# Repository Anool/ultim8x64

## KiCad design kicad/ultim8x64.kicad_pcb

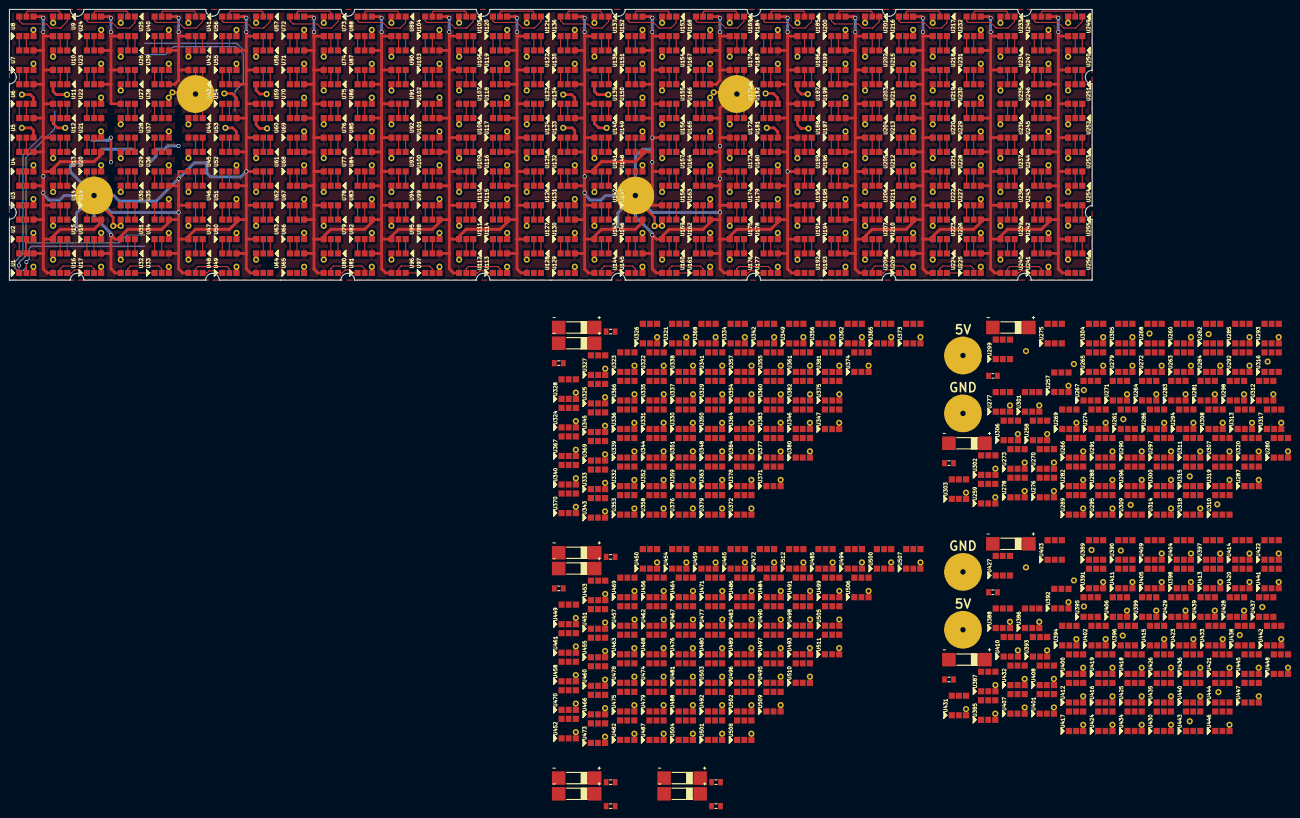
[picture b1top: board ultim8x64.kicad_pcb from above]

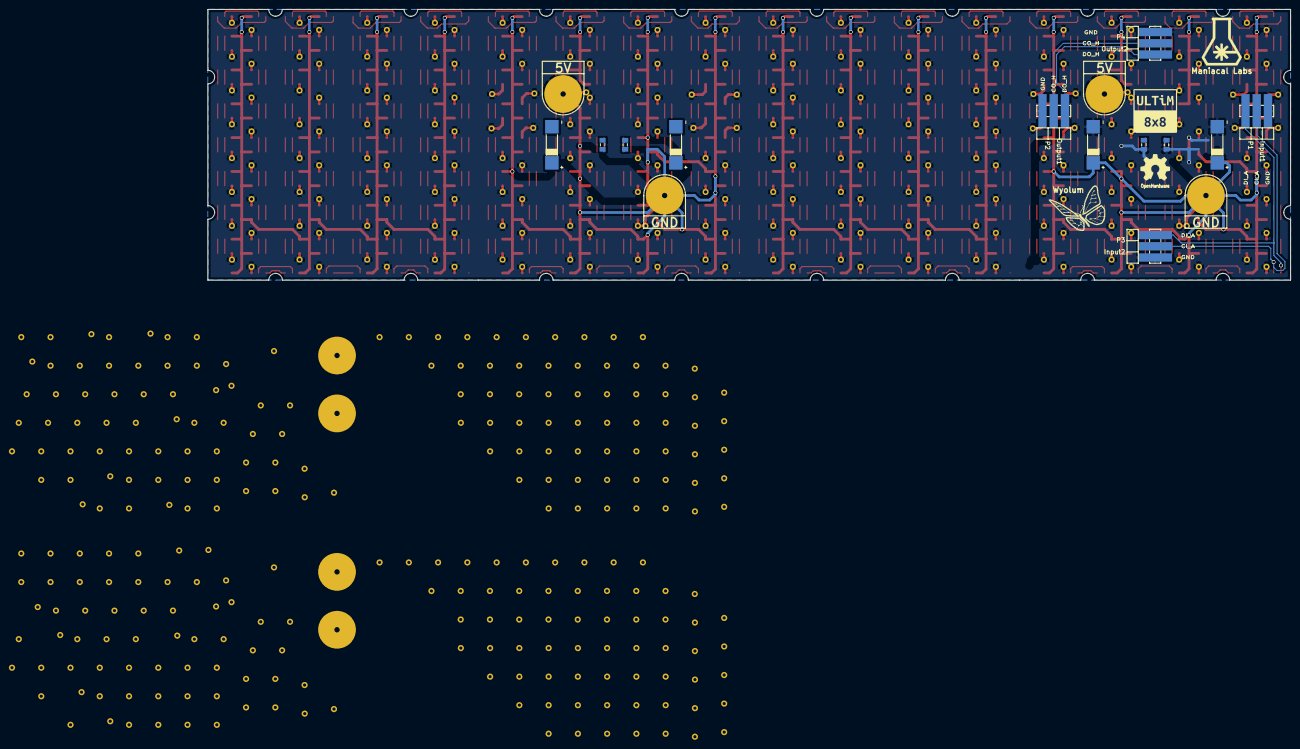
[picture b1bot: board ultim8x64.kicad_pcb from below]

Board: 2 copper layers, 243.8 x 61.0 mm, 560 parts (20 on the bottom side), 1036 nets.

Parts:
C1, C2, C5, C6, C9, C10, C13, C14, C17, C18, C21, C22, C25, C26, C29, C30: 47uF 20V; c_2917
C3, C4, C7, C8, C11, C12, C15, C16, C19, C20, C23, C24, C27, C28, C31, C32: 100nF; c_0805
L1: ULTiM8x8; logo_ultim8x8
L2: OSHW; OSHW_6mm
L3: Wyolum; logo_wyo_butterfly
L4: Maniacal Labs; logo_MLlabs
P1: Input1; header_3pos_smd_male
P2: Output1; header_3pos_smd_male
P3: Input2; header_3pos_smd_male
P4: Output2; header_3pos_smd_male
P5, P7, P9, P11: GND; PowerIn_stud
P6, P8, P10, P12: 5V; PowerIn_stud
U1, U2, U3, U4, U7, U8, U9, U10, U13, U14, U15, U16, U17, U18, U20, U21, U22, U23, U24, U25, U26, U27, U28, U29, U30, U31, U32, U33, U34, U35, U36, U37, U39, U40, U41, U42, U44, U45, U46, U47, U48, U49, U50, U51, U52, U55, U56, U57, U58, U61, U62, U63, U64, U65, U66, U67, U68, U69, U70, U71, U72, U73, U74, U75, U76, U77, U78, U79, U80, U81, U82, U83, U84, U85, U86, U87, U88, U89, U90, U91, U92, U93, U94, U95, U96, U97, U98, U99, U100, U101, U102, U103, U104, U105, U106, U107, U108, U109, U110, U111, U112, U113, U114, U115, U116, U117, U118, U119, U120, U121, U122, U123, U124, U125, U126, U127, U128, U129, U130, U131, U132, U135, U136, U137, U138, U141, U142, U143, U144, U145, U146, U148, U149, U150, U151, U152, U153, U154, U155, U156, U157, U158, U159, U160, U161, U162, U163, U164, U165, U167, U168, U169, U170, U172, U173, U174, U175, U176, U177, U178, U179, U180, U183, U184, U185, U186, U189, U190, U191, U192, U193, U194, U195, U196, U197, U198, U199, U200, U201, U202, U203, U204, U205, U206, U207, U208, U209, U210, U211, U212, U213, U214, U215, U216, U217, U218, U219, U220, U221, U222, U223, U224, U225, U226, U227, U228, U229, U230, U231, U232, U233, U234, U235, U236, U237, U238, U239, U240, U241, U242, U243, U244, U245, U246, U247, U248, U249, U250, U251, U252, U253, U254, U255, U256, U257, U258, U259, U260, U263, U264, U265, U266, U269, U270, U271, U272, U273, U274, U276, U277, U278, U279, U280, U281, U282, U283, U284, U285, U286, U287, U288, U289, U290, U291, U292, U293, U295, U296, U297, U298, U300, U301, U302, U303, U304, U305, U306, U307, U308, U311, U312, U313, U314, U317, U318, U319, U320, U321, U322, U323, U324, U325, U326, U327, U328, U329, U330, U331, U332, U333, U334, U335, U336, U337, U338, U339, U340, U341, U342, U343, U344, U345, U346, U347, U348, U349, U350, U351, U352, U353, U354, U355, U356, U357, U358, U359, U360, U361, U362, U363, U364, U365, U366, U367, U368, U369, U370, U371, U372, U373, U374, U375, U376, U377, U378, U379, U380, U381, U382, U383, U384, U385, U386, U387, U388, U391, U392, U393, U394, U397, U398, U399, U400, U401, U402, U404, U405, U406, U407, U408, U409, U410, U411, U412, U413, U414, U415, U416, U417, U418, U419, U420, U421, U423, U424, U425, U426, U428, U429, U430, U431, U432, U433, U434, U435, U436, U439, U440, U441, U442, U445, U446, U447, U448, U449, U450, U451, U452, U453, U454, U455, U456, U457, U458, U459, U460, U461, U462, U463, U464, U465, U466, U467, U468, U469, U470, U471, U472, U473, U474, U475, U476, U477, U478, U479, U480, U481, U482, U483, U484, U485, U486, U487, U488, U489, U490, U491, U492, U493, U494, U495, U496, U497, U498, U499, U500, U501, U502, U503, U504, U505, U506, U507, U508, U509, U510, U511, U512: APA102
U5, U133, U261, U389: APA102; APA102_U05
U6, U134, U262, U390: APA102; APA102_U06
U11, U139, U267, U395: APA102; APA102_U11
U12, U140, U268, U396: APA102; APA102_U12
U19, U147, U275, U403: APA102; APA102_U19
U38, U166, U294, U422: APA102; APA102_U38
U43, U171, U299, U427: APA102; APA102_U43
U53, U181, U309, U437: APA102; APA102_U53
U54, U182, U310, U438: APA102; APA102_U54
U59, U187, U315, U443: APA102; APA102_U59
U60, U188, U316, U444: APA102; APA102_U60

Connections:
/Row_A/5V: C1.1, C2.1, C3.1, C4.1, C9.1, C10.1, C11.1, C12.1, C17.1, C18.1, C19.1, C20.1, C25.1, C26.1, C27.1, C28.1, P5.1, P7.1, P9.1, P11.1, U1.4, U2.4, U3.4, U4.4, U5.4, U6.4, U7.4, U8.4, U9.4, U10.4, U11.4, U12.4, U13.4, U14.4, U15.4, U16.4, U17.4, U18.4, U19.4, U20.4, U21.4, U22.4, U23.4, U24.4, U25.4, U26.4, U27.4, U28.4, U29.4, U30.4, U31.4, U32.4, U33.4, U34.4, U35.4, U36.4, U37.4, U38.4, U39.4, U40.4, U41.4, U42.4, U43.4, U44.4, U45.4, U46.4, U47.4, U48.4, U49.4, U50.4, U51.4, U52.4, U53.4, U54.4, U55.4, U56.4, U57.4, U58.4, U59.4, U60.4, U61.4, U62.4, U63.4, U64.4, U65.4, U66.4, U67.4, U68.4, U69.4, U70.4, U71.4, U72.4, U73.4, U74.4, U75.4, U76.4, U77.4, U78.4, U79.4, U80.4, U81.4, U82.4, U83.4, U84.4, U85.4, U86.4, U87.4, U88.4, U89.4, U90.4, U91.4, U92.4, U93.4, U94.4, U95.4, U96.4, U97.4, U98.4, U99.4, U100.4, U101.4, U102.4, U103.4, U104.4, U105.4, U106.4, U107.4, U108.4, U109.4, U110.4, U111.4, U112.4, U113.4, U114.4, U115.4, U116.4, U117.4, U118.4, U119.4, U120.4, U121.4, U122.4, U123.4, U124.4, U125.4, U126.4, U127.4, U128.4, U129.4, U130.4, U131.4, U132.4, U133.4, U134.4, U135.4, U136.4, U137.4, U138.4, U139.4, U140.4, U141.4, U142.4, U143.4, U144.4, U145.4, U146.4, U147.4, U148.4, U149.4, U150.4, U151.4, U152.4, U153.4, U154.4, U155.4, U156.4, U157.4, U158.4, U159.4, U160.4, U161.4, U162.4, U163.4, U164.4, U165.4, U166.4, U167.4, U168.4, U169.4, U170.4, U171.4, U172.4, U173.4, U174.4, U175.4, U176.4, U177.4, U178.4, U179.4, U180.4, U181.4, U182.4, U183.4, U184.4, U185.4, U186.4, U187.4, U188.4, U189.4, U190.4, U191.4, U192.4, U193.4, U194.4, U195.4, U196.4, U197.4, U198.4, U199.4, U200.4, U201.4, U202.4, U203.4, U204.4, U205.4, U206.4, U207.4, U208.4, U209.4, U210.4, U211.4, U212.4, U213.4, U214.4, U215.4, U216.4, U217.4, U218.4, U219.4, U220.4, U221.4, U222.4, U223.4, U224.4, U225.4, U226.4, U227.4, U228.4, U229.4, U230.4, U231.4, U232.4, U233.4, U234.4, U235.4, U236.4, U237.4, U238.4, U239.4, U240.4, U241.4, U242.4, U243.4, U244.4, U245.4, U246.4, U247.4, U248.4, U249.4, U250.4, U251.4, U252.4, U253.4, U254.4, U255.4, U256.4, U257.4, U258.4, U259.4, U260.4, U261.4, U262.4, U263.4, U264.4, U265.4, U266.4, U267.4, U268.4, U269.4, U270.4, U271.4, U272.4, U273.4, U274.4, U275.4, U276.4, U277.4, U278.4, U279.4, U280.4, U281.4, U282.4, U283.4, U284.4, U285.4, U286.4, U287.4, U288.4, U289.4, U290.4, U291.4, U292.4, U293.4, U294.4, U295.4, U296.4, U297.4, U298.4, U299.4, U300.4, U301.4, U302.4, U303.4, U304.4, U305.4, U306.4, U307.4, U308.4, U309.4, U310.4, U311.4, U312.4, U313.4, U314.4, U315.4, U316.4, U317.4, U318.4, U319.4, U320.4, U321.4, U322.4, U323.4, U324.4, U325.4, U326.4, U327.4, U328.4, U329.4, U330.4, U331.4, U332.4, U333.4, U334.4, U335.4, U336.4, U337.4, U338.4, U339.4, U340.4, U341.4, U342.4, U343.4, U344.4, U345.4, U346.4, U347.4, U348.4, U349.4, U350.4, U351.4, U352.4, U353.4, U354.4, U355.4, U356.4, U357.4, U358.4, U359.4, U360.4, U361.4, U362.4, U363.4, U364.4, U365.4, U366.4, U367.4, U368.4, U369.4, U370.4, U371.4, U372.4, U373.4, U374.4, U375.4, U376.4, U377.4, U378.4, U379.4, U380.4, U381.4, U382.4, U383.4, U384.4, U385.4, U386.4, U387.4, U388.4, U389.4, U390.4, U391.4, U392.4, U393.4, U394.4, U395.4, U396.4, U397.4, U398.4, U399.4, U400.4, U401.4, U402.4, U403.4, U404.4, U405.4, U406.4, U407.4, U408.4, U409.4, U410.4, U411.4, U412.4, U413.4, U414.4, U415.4, U416.4, U417.4, U418.4, U419.4, U420.4, U421.4, U422.4, U423.4, U424.4, U425.4, U426.4, U427.4, U428.4, U429.4, U430.4, U431.4, U432.4, U433.4, U434.4, U435.4, U436.4, U437.4, U438.4, U439.4, U440.4, U441.4, U442.4, U443.4, U444.4, U445.4, U446.4, U447.4, U448.4, U449.4, U450.4, U451.4, U452.4, U453.4, U454.4, U455.4, U456.4, U457.4, U458.4, U459.4, U460.4, U461.4, U462.4, U463.4, U464.4, U465.4, U466.4, U467.4, U468.4, U469.4, U470.4, U471.4, U472.4, U473.4, U474.4, U475.4, U476.4, U477.4, U478.4, U479.4, U480.4, U481.4, U482.4, U483.4, U484.4, U485.4, U486.4, U487.4, U488.4, U489.4, U490.4, U491.4, U492.4, U493.4, U494.4, U495.4, U496.4, U497.4, U498.4, U499.4, U500.4, U501.4, U502.4, U503.4, U504.4, U505.4, U506.4, U507.4, U508.4, U509.4, U510.4, U511.4, U512.4
/Row_A/CI_A: P1.2, P3.2, U1.2
/Row_A/CI_B: U64.5, U65.2
/Row_A/DI_A: P1.1, P3.1, U1.1
/Row_A/DI_B: U64.6, U65.1
/Row_B/CI_C: U128.5, U129.2
/Row_B/DI_C: U128.6, U129.1
/Row_C/CI_D: U192.5, U193.2
/Row_C/DI_D: U192.6, U193.1
/Row_D/CI_E: U256.5, U257.2
/Row_D/DI_E: U256.6, U257.1
/Row_E/CI_F: U320.5, U321.2
/Row_E/DI_F: U320.6, U321.1
/Row_F/CI_G: U384.5, U385.2
/Row_F/DI_G: U384.6, U385.1
/Row_G/CI_H: U448.5, U449.2
/Row_G/DI_H: U448.6, U449.1
/Row_H/CO_H: P2.2, P4.2, U512.5
/Row_H/DO_H: P2.3, P4.3, U512.6
GND: C1.2, C2.2, C3.2, C4.2, C9.2, C10.2, C11.2, C12.2, C17.2, C18.2, C19.2, C20.2, C25.2, C26.2, C27.2, C28.2, P1.3, P2.1, P3.3, P4.1, P6.1, P8.1, P10.1, P12.1, U1.3, U2.3, U3.3, U4.3, U5.3, U6.3, U7.3, U8.3, U9.3, U10.3, U11.3, U12.3, U13.3, U14.3, U15.3, U16.3, U17.3, U18.3, U19.3, U20.3, U21.3, U22.3, U23.3, U24.3, U25.3, U26.3, U27.3, U28.3, U29.3, U30.3, U31.3, U32.3, U33.3, U34.3, U35.3, U36.3, U37.3, U38.3, U39.3, U40.3, U41.3, U42.3, U43.3, U44.3, U45.3, U46.3, U47.3, U48.3, U49.3, U50.3, U51.3, U52.3, U53.3, U54.3, U55.3, U56.3, U57.3, U58.3, U59.3, U60.3, U61.3, U62.3, U63.3, U64.3, U65.3, U66.3, U67.3, U68.3, U69.3, U70.3, U71.3, U72.3, U73.3, U74.3, U75.3, U76.3, U77.3, U78.3, U79.3, U80.3, U81.3, U82.3, U83.3, U84.3, U85.3, U86.3, U87.3, U88.3, U89.3, U90.3, U91.3, U92.3, U93.3, U94.3, U95.3, U96.3, U97.3, U98.3, U99.3, U100.3, U101.3, U102.3, U103.3, U104.3, U105.3, U106.3, U107.3, U108.3, U109.3, U110.3, U111.3, U112.3, U113.3, U114.3, U115.3, U116.3, U117.3, U118.3, U119.3, U120.3, U121.3, U122.3, U123.3, U124.3, U125.3, U126.3, U127.3, U128.3, U129.3, U130.3, U131.3, U132.3, U133.3, U134.3, U135.3, U136.3, U137.3, U138.3, U139.3, U140.3, U141.3, U142.3, U143.3, U144.3, U145.3, U146.3, U147.3, U148.3, U149.3, U150.3, U151.3, U152.3, U153.3, U154.3, U155.3, U156.3, U157.3, U158.3, U159.3, U160.3, U161.3, U162.3, U163.3, U164.3, U165.3, U166.3, U167.3, U168.3, U169.3, U170.3, U171.3, U172.3, U173.3, U174.3, U175.3, U176.3, U177.3, U178.3, U179.3, U180.3, U181.3, U182.3, U183.3, U184.3, U185.3, U186.3, U187.3, U188.3, U189.3, U190.3, U191.3, U192.3, U193.3, U194.3, U195.3, U196.3, U197.3, U198.3, U199.3, U200.3, U201.3, U202.3, U203.3, U204.3, U205.3, U206.3, U207.3, U208.3, U209.3, U210.3, U211.3, U212.3, U213.3, U214.3, U215.3, U216.3, U217.3, U218.3, U219.3, U220.3, U221.3, U222.3, U223.3, U224.3, U225.3, U226.3, U227.3, U228.3, U229.3, U230.3, U231.3, U232.3, U233.3, U234.3, U235.3, U236.3, U237.3, U238.3, U239.3, U240.3, U241.3, U242.3, U243.3, U244.3, U245.3, U246.3, U247.3, U248.3, U249.3, U250.3, U251.3, U252.3, U253.3, U254.3, U255.3, U256.3, U257.3, U258.3, U259.3, U260.3, U261.3, U262.3, U263.3, U264.3, U265.3, U266.3, U267.3, U268.3, U269.3, U270.3, U271.3, U272.3, U273.3, U274.3, U275.3, U276.3, U277.3, U278.3, U279.3, U280.3, U281.3, U282.3, U283.3, U284.3, U285.3, U286.3, U287.3, U288.3, U289.3, U290.3, U291.3, U292.3, U293.3, U294.3, U295.3, U296.3, U297.3, U298.3, U299.3, U300.3, U301.3, U302.3, U303.3, U304.3, U305.3, U306.3, U307.3, U308.3, U309.3, U310.3, U311.3, U312.3, U313.3, U314.3, U315.3, U316.3, U317.3, U318.3, U319.3, U320.3, U321.3, U322.3, U323.3, U324.3, U325.3, U326.3, U327.3, U328.3, U329.3, U330.3, U331.3, U332.3, U333.3, U334.3, U335.3, U336.3, U337.3, U338.3, U339.3, U340.3, U341.3, U342.3, U343.3, U344.3, U345.3, U346.3, U347.3, U348.3, U349.3, U350.3, U351.3, U352.3, U353.3, U354.3, U355.3, U356.3, U357.3, U358.3, U359.3, U360.3, U361.3, U362.3, U363.3, U364.3, U365.3, U366.3, U367.3, U368.3, U369.3, U370.3, U371.3, U372.3, U373.3, U374.3, U375.3, U376.3, U377.3, U378.3, U379.3, U380.3, U381.3, U382.3, U383.3, U384.3, U385.3, U386.3, U387.3, U388.3, U389.3, U390.3, U391.3, U392.3, U393.3, U394.3, U395.3, U396.3, U397.3, U398.3, U399.3, U400.3, U401.3, U402.3, U403.3, U404.3, U405.3, U406.3, U407.3, U408.3, U409.3, U410.3, U411.3, U412.3, U413.3, U414.3, U415.3, U416.3, U417.3, U418.3, U419.3, U420.3, U421.3, U422.3, U423.3, U424.3, U425.3, U426.3, U427.3, U428.3, U429.3, U430.3, U431.3, U432.3, U433.3, U434.3, U435.3, U436.3, U437.3, U438.3, U439.3, U440.3, U441.3, U442.3, U443.3, U444.3, U445.3, U446.3, U447.3, U448.3, U449.3, U450.3, U451.3, U452.3, U453.3, U454.3, U455.3, U456.3, U457.3, U458.3, U459.3, U460.3, U461.3, U462.3, U463.3, U464.3, U465.3, U466.3, U467.3, U468.3, U469.3, U470.3, U471.3, U472.3, U473.3, U474.3, U475.3, U476.3, U477.3, U478.3, U479.3, U480.3, U481.3, U482.3, U483.3, U484.3, U485.3, U486.3, U487.3, U488.3, U489.3, U490.3, U491.3, U492.3, U493.3, U494.3, U495.3, U496.3, U497.3, U498.3, U499.3, U500.3, U501.3, U502.3, U503.3, U504.3, U505.3, U506.3, U507.3, U508.3, U509.3, U510.3, U511.3, U512.3
unnamed: C5.1, C6.1, C7.1, C8.1
unnamed: C5.2, C6.2, C7.2, C8.2
unnamed: C13.1, C14.1, C15.1, C16.1
unnamed: C13.2, C14.2, C15.2, C16.2
unnamed: C21.1, C22.1, C23.1, C24.1
unnamed: C21.2, C22.2, C23.2, C24.2
unnamed: C29.1, C30.1, C31.1, C32.1
unnamed: C29.2, C30.2, C31.2, C32.2
unnamed: U1.5, U2.2
unnamed: U1.6, U2.1
unnamed: U2.5, U3.2
unnamed: U2.6, U3.1
unnamed: U3.5, U4.2
unnamed: U3.6, U4.1
unnamed: U4.5, U5.2
unnamed: U4.6, U5.1
unnamed: U5.5, U6.2
unnamed: U5.6, U6.1
unnamed: U6.5, U7.2
unnamed: U6.6, U7.1
unnamed: U7.5, U8.2
unnamed: U7.6, U8.1
unnamed: U8.5, U9.2
unnamed: U8.6, U9.1
unnamed: U9.6, U10.1
unnamed: U9.5, U10.2
unnamed: U10.5, U11.2
unnamed: U10.6, U11.1
unnamed: U11.5, U12.2
unnamed: U11.6, U12.1
unnamed: U12.5, U13.2
unnamed: U12.6, U13.1
unnamed: U13.5, U14.2
unnamed: U13.6, U14.1
unnamed: U14.5, U15.2
unnamed: U14.6, U15.1
unnamed: U15.5, U16.2
unnamed: U15.6, U16.1
unnamed: U16.5, U17.2
unnamed: U16.6, U17.1
unnamed: U17.5, U18.2
unnamed: U17.6, U18.1
unnamed: U18.5, U19.2
unnamed: U18.6, U19.1
unnamed: U19.5, U20.2
unnamed: U19.6, U20.1
unnamed: U20.5, U21.2
unnamed: U20.6, U21.1
unnamed: U21.5, U22.2
unnamed: U21.6, U22.1
unnamed: U22.5, U23.2
unnamed: U22.6, U23.1
unnamed: U23.5, U24.2
unnamed: U23.6, U24.1
unnamed: U24.5, U25.2
unnamed: U24.6, U25.1
unnamed: U25.5, U26.2
unnamed: U25.6, U26.1
unnamed: U26.5, U27.2
unnamed: U26.6, U27.1
unnamed: U27.5, U28.2
unnamed: U27.6, U28.1
unnamed: U28.5, U29.2
unnamed: U28.6, U29.1
unnamed: U29.5, U30.2
unnamed: U29.6, U30.1
unnamed: U30.5, U31.2
unnamed: U30.6, U31.1
unnamed: U31.5, U32.2
unnamed: U31.6, U32.1
unnamed: U32.5, U33.2
unnamed: U32.6, U33.1
unnamed: U33.5, U34.2
unnamed: U33.6, U34.1
unnamed: U34.5, U35.2
unnamed: U34.6, U35.1
unnamed: U35.5, U36.2
unnamed: U35.6, U36.1
unnamed: U36.5, U37.2
unnamed: U36.6, U37.1
unnamed: U37.5, U38.2
unnamed: U37.6, U38.1
unnamed: U38.5, U39.2
unnamed: U38.6, U39.1
unnamed: U39.5, U40.2
unnamed: U39.6, U40.1
unnamed: U40.5, U41.2
unnamed: U40.6, U41.1
unnamed: U41.5, U42.2
unnamed: U41.6, U42.1
unnamed: U42.5, U43.2
unnamed: U42.6, U43.1
unnamed: U43.5, U44.2
unnamed: U43.6, U44.1
unnamed: U44.5, U45.2
unnamed: U44.6, U45.1
unnamed: U45.5, U46.2
unnamed: U45.6, U46.1
unnamed: U46.5, U47.2
unnamed: U46.6, U47.1
unnamed: U47.5, U48.2
unnamed: U47.6, U48.1
unnamed: U48.5, U49.2
unnamed: U48.6, U49.1
unnamed: U49.5, U50.2
unnamed: U49.6, U50.1
unnamed: U50.5, U51.2
unnamed: U50.6, U51.1
unnamed: U51.5, U52.2
unnamed: U51.6, U52.1
unnamed: U52.5, U53.2
unnamed: U52.6, U53.1
unnamed: U53.5, U54.2
unnamed: U53.6, U54.1
unnamed: U54.5, U55.2
unnamed: U54.6, U55.1
unnamed: U55.5, U56.2
unnamed: U55.6, U56.1
unnamed: U56.5, U57.2
unnamed: U56.6, U57.1
unnamed: U57.5, U58.2
unnamed: U57.6, U58.1
unnamed: U58.5, U59.2
unnamed: U58.6, U59.1
unnamed: U59.5, U60.2
unnamed: U59.6, U60.1
unnamed: U60.5, U61.2
unnamed: U60.6, U61.1
unnamed: U61.5, U62.2
unnamed: U61.6, U62.1
unnamed: U62.5, U63.2
unnamed: U62.6, U63.1
unnamed: U63.5, U64.2
unnamed: U63.6, U64.1
unnamed: U65.5, U66.2
unnamed: U65.6, U66.1
unnamed: U66.5, U67.2
unnamed: U66.6, U67.1
unnamed: U67.5, U68.2
unnamed: U67.6, U68.1
unnamed: U68.5, U69.2
unnamed: U68.6, U69.1
unnamed: U69.5, U70.2
unnamed: U69.6, U70.1
unnamed: U70.5, U71.2
unnamed: U70.6, U71.1
unnamed: U71.5, U72.2
unnamed: U71.6, U72.1
unnamed: U72.5, U73.2
unnamed: U72.6, U73.1
unnamed: U73.5, U74.2
unnamed: U73.6, U74.1
unnamed: U74.5, U75.2
unnamed: U74.6, U75.1
unnamed: U75.5, U76.2
unnamed: U75.6, U76.1
unnamed: U76.5, U77.2
unnamed: U76.6, U77.1
unnamed: U77.5, U78.2
unnamed: U77.6, U78.1
unnamed: U78.5, U79.2
unnamed: U78.6, U79.1
unnamed: U79.5, U80.2
unnamed: U79.6, U80.1
unnamed: U80.5, U81.2
unnamed: U80.6, U81.1
unnamed: U81.5, U82.2
unnamed: U81.6, U82.1
unnamed: U82.5, U83.2
unnamed: U82.6, U83.1
unnamed: U83.5, U84.2
unnamed: U83.6, U84.1
unnamed: U84.5, U85.2
unnamed: U84.6, U85.1
unnamed: U85.5, U86.2
unnamed: U85.6, U86.1
unnamed: U86.5, U87.2
unnamed: U86.6, U87.1
unnamed: U87.5, U88.2
unnamed: U87.6, U88.1
unnamed: U88.5, U89.2
unnamed: U88.6, U89.1
unnamed: U89.5, U90.2
unnamed: U89.6, U90.1
unnamed: U90.5, U91.2
unnamed: U90.6, U91.1
unnamed: U91.5, U92.2
unnamed: U91.6, U92.1
unnamed: U92.5, U93.2
unnamed: U92.6, U93.1
unnamed: U93.5, U94.2
unnamed: U93.6, U94.1
unnamed: U94.5, U95.2
unnamed: U94.6, U95.1
unnamed: U95.5, U96.2
unnamed: U95.6, U96.1
unnamed: U96.5, U97.2
unnamed: U96.6, U97.1
unnamed: U97.5, U98.2
unnamed: U97.6, U98.1
unnamed: U98.5, U99.2
unnamed: U98.6, U99.1
unnamed: U99.6, U100.1
unnamed: U99.5, U100.2
unnamed: U100.5, U101.2
unnamed: U100.6, U101.1
unnamed: U101.5, U102.2
unnamed: U101.6, U102.1
unnamed: U102.5, U103.2
unnamed: U102.6, U103.1
unnamed: U103.5, U104.2
unnamed: U103.6, U104.1
unnamed: U104.5, U105.2
unnamed: U104.6, U105.1
unnamed: U105.5, U106.2
unnamed: U105.6, U106.1
unnamed: U106.5, U107.2
unnamed: U106.6, U107.1
unnamed: U107.5, U108.2
unnamed: U107.6, U108.1
unnamed: U108.5, U109.2
unnamed: U108.6, U109.1
unnamed: U109.5, U110.2
unnamed: U109.6, U110.1
unnamed: U110.5, U111.2
unnamed: U110.6, U111.1
unnamed: U111.5, U112.2
unnamed: U111.6, U112.1
unnamed: U112.5, U113.2
unnamed: U112.6, U113.1
unnamed: U113.5, U114.2
unnamed: U113.6, U114.1
unnamed: U114.5, U115.2
unnamed: U114.6, U115.1
unnamed: U115.5, U116.2
unnamed: U115.6, U116.1
unnamed: U116.5, U117.2
unnamed: U116.6, U117.1
unnamed: U117.5, U118.2
unnamed: U117.6, U118.1
unnamed: U118.5, U119.2
unnamed: U118.6, U119.1
unnamed: U119.5, U120.2
unnamed: U119.6, U120.1
unnamed: U120.5, U121.2
unnamed: U120.6, U121.1
unnamed: U121.5, U122.2
unnamed: U121.6, U122.1
unnamed: U122.5, U123.2
unnamed: U122.6, U123.1
unnamed: U123.5, U124.2
unnamed: U123.6, U124.1
unnamed: U124.5, U125.2
unnamed: U124.6, U125.1
unnamed: U125.5, U126.2
unnamed: U125.6, U126.1
unnamed: U126.5, U127.2
unnamed: U126.6, U127.1
unnamed: U127.5, U128.2
unnamed: U127.6, U128.1
unnamed: U129.5, U130.2
unnamed: U129.6, U130.1
unnamed: U130.5, U131.2
unnamed: U130.6, U131.1
unnamed: U131.5, U132.2
unnamed: U131.6, U132.1
unnamed: U132.5, U133.2
unnamed: U132.6, U133.1
unnamed: U133.5, U134.2
unnamed: U133.6, U134.1
unnamed: U134.5, U135.2
unnamed: U134.6, U135.1
unnamed: U135.5, U136.2
unnamed: U135.6, U136.1
unnamed: U136.5, U137.2
unnamed: U136.6, U137.1
unnamed: U137.5, U138.2
unnamed: U137.6, U138.1
unnamed: U138.5, U139.2
unnamed: U138.6, U139.1
unnamed: U139.5, U140.2
unnamed: U139.6, U140.1
unnamed: U140.5, U141.2
unnamed: U140.6, U141.1
unnamed: U141.5, U142.2
unnamed: U141.6, U142.1
unnamed: U142.5, U143.2
unnamed: U142.6, U143.1
unnamed: U143.5, U144.2
unnamed: U143.6, U144.1
unnamed: U144.5, U145.2
unnamed: U144.6, U145.1
unnamed: U145.5, U146.2
unnamed: U145.6, U146.1
unnamed: U146.5, U147.2
unnamed: U146.6, U147.1
unnamed: U147.5, U148.2
unnamed: U147.6, U148.1
unnamed: U148.5, U149.2
unnamed: U148.6, U149.1
unnamed: U149.5, U150.2
unnamed: U149.6, U150.1
unnamed: U150.5, U151.2
unnamed: U150.6, U151.1
unnamed: U151.5, U152.2
unnamed: U151.6, U152.1
unnamed: U152.5, U153.2
unnamed: U152.6, U153.1
unnamed: U153.5, U154.2
unnamed: U153.6, U154.1
unnamed: U154.5, U155.2
unnamed: U154.6, U155.1
unnamed: U155.5, U156.2
unnamed: U155.6, U156.1
unnamed: U156.5, U157.2
unnamed: U156.6, U157.1
unnamed: U157.5, U158.2
unnamed: U157.6, U158.1
unnamed: U158.5, U159.2
unnamed: U158.6, U159.1
unnamed: U159.5, U160.2
unnamed: U159.6, U160.1
unnamed: U160.5, U161.2
unnamed: U160.6, U161.1
unnamed: U161.5, U162.2
unnamed: U161.6, U162.1
unnamed: U162.5, U163.2
unnamed: U162.6, U163.1
unnamed: U163.5, U164.2
unnamed: U163.6, U164.1
unnamed: U164.5, U165.2
unnamed: U164.6, U165.1
unnamed: U165.5, U166.2
unnamed: U165.6, U166.1
unnamed: U166.5, U167.2
unnamed: U166.6, U167.1
unnamed: U167.5, U168.2
unnamed: U167.6, U168.1
unnamed: U168.5, U169.2
unnamed: U168.6, U169.1
unnamed: U169.5, U170.2
unnamed: U169.6, U170.1
unnamed: U170.5, U171.2
unnamed: U170.6, U171.1
unnamed: U171.5, U172.2
unnamed: U171.6, U172.1
unnamed: U172.5, U173.2
unnamed: U172.6, U173.1
unnamed: U173.5, U174.2
unnamed: U173.6, U174.1
unnamed: U174.5, U175.2
unnamed: U174.6, U175.1
unnamed: U175.5, U176.2
unnamed: U175.6, U176.1
unnamed: U176.5, U177.2
unnamed: U176.6, U177.1
unnamed: U177.5, U178.2
unnamed: U177.6, U178.1
unnamed: U178.5, U179.2
unnamed: U178.6, U179.1
unnamed: U179.5, U180.2
unnamed: U179.6, U180.1
unnamed: U180.5, U181.2
unnamed: U180.6, U181.1
unnamed: U181.5, U182.2
unnamed: U181.6, U182.1
unnamed: U182.5, U183.2
unnamed: U182.6, U183.1
unnamed: U183.5, U184.2
unnamed: U183.6, U184.1
unnamed: U184.5, U185.2
unnamed: U184.6, U185.1
unnamed: U185.5, U186.2
unnamed: U185.6, U186.1
unnamed: U186.5, U187.2
unnamed: U186.6, U187.1
unnamed: U187.5, U188.2
unnamed: U187.6, U188.1
unnamed: U188.5, U189.2
unnamed: U188.6, U189.1
unnamed: U189.5, U190.2
unnamed: U189.6, U190.1
unnamed: U190.5, U191.2
unnamed: U190.6, U191.1
unnamed: U191.5, U192.2
unnamed: U191.6, U192.1
unnamed: U193.5, U194.2
unnamed: U193.6, U194.1
unnamed: U194.5, U195.2
unnamed: U194.6, U195.1
unnamed: U195.5, U196.2
unnamed: U195.6, U196.1
unnamed: U196.5, U197.2
unnamed: U196.6, U197.1
unnamed: U197.5, U198.2
unnamed: U197.6, U198.1
unnamed: U198.5, U199.2
unnamed: U198.6, U199.1
unnamed: U199.5, U200.2
unnamed: U199.6, U200.1
unnamed: U200.5, U201.2
unnamed: U200.6, U201.1
unnamed: U201.5, U202.2
unnamed: U201.6, U202.1
unnamed: U202.5, U203.2
unnamed: U202.6, U203.1
unnamed: U203.5, U204.2
unnamed: U203.6, U204.1
unnamed: U204.5, U205.2
unnamed: U204.6, U205.1
unnamed: U205.5, U206.2
unnamed: U205.6, U206.1
unnamed: U206.5, U207.2
unnamed: U206.6, U207.1
unnamed: U207.5, U208.2
unnamed: U207.6, U208.1
unnamed: U208.5, U209.2
unnamed: U208.6, U209.1
unnamed: U209.5, U210.2
unnamed: U209.6, U210.1
unnamed: U210.5, U211.2
unnamed: U210.6, U211.1
unnamed: U211.5, U212.2
unnamed: U211.6, U212.1
unnamed: U212.5, U213.2
unnamed: U212.6, U213.1
unnamed: U213.5, U214.2
unnamed: U213.6, U214.1
unnamed: U214.5, U215.2
unnamed: U214.6, U215.1
unnamed: U215.5, U216.2
unnamed: U215.6, U216.1
unnamed: U216.5, U217.2
unnamed: U216.6, U217.1
unnamed: U217.5, U218.2
unnamed: U217.6, U218.1
unnamed: U218.5, U219.2
unnamed: U218.6, U219.1
unnamed: U219.5, U220.2
unnamed: U219.6, U220.1
unnamed: U220.5, U221.2
unnamed: U220.6, U221.1
unnamed: U221.5, U222.2
unnamed: U221.6, U222.1
unnamed: U222.5, U223.2
unnamed: U222.6, U223.1
unnamed: U223.5, U224.2
unnamed: U223.6, U224.1
unnamed: U224.5, U225.2
unnamed: U224.6, U225.1
unnamed: U225.5, U226.2
unnamed: U225.6, U226.1
unnamed: U226.5, U227.2
unnamed: U226.6, U227.1
unnamed: U227.5, U228.2
unnamed: U227.6, U228.1
unnamed: U228.5, U229.2
unnamed: U228.6, U229.1
unnamed: U229.5, U230.2
unnamed: U229.6, U230.1
unnamed: U230.5, U231.2
unnamed: U230.6, U231.1
unnamed: U231.5, U232.2
unnamed: U231.6, U232.1
unnamed: U232.5, U233.2
unnamed: U232.6, U233.1
unnamed: U233.5, U234.2
unnamed: U233.6, U234.1
unnamed: U234.5, U235.2
unnamed: U234.6, U235.1
unnamed: U235.5, U236.2
unnamed: U235.6, U236.1
unnamed: U236.5, U237.2
unnamed: U236.6, U237.1
unnamed: U237.5, U238.2
unnamed: U237.6, U238.1
unnamed: U238.5, U239.2
unnamed: U238.6, U239.1
unnamed: U239.5, U240.2
unnamed: U239.6, U240.1
unnamed: U240.5, U241.2
unnamed: U240.6, U241.1
unnamed: U241.5, U242.2
unnamed: U241.6, U242.1
unnamed: U242.5, U243.2
unnamed: U242.6, U243.1
unnamed: U243.5, U244.2
unnamed: U243.6, U244.1
unnamed: U244.5, U245.2
unnamed: U244.6, U245.1
unnamed: U245.5, U246.2
unnamed: U245.6, U246.1
unnamed: U246.5, U247.2
unnamed: U246.6, U247.1
unnamed: U247.5, U248.2
unnamed: U247.6, U248.1
unnamed: U248.5, U249.2
unnamed: U248.6, U249.1
unnamed: U249.5, U250.2
unnamed: U249.6, U250.1
unnamed: U250.5, U251.2
unnamed: U250.6, U251.1
unnamed: U251.5, U252.2
unnamed: U251.6, U252.1
unnamed: U252.5, U253.2
unnamed: U252.6, U253.1
unnamed: U253.5, U254.2
unnamed: U253.6, U254.1
unnamed: U254.5, U255.2
unnamed: U254.6, U255.1
unnamed: U255.5, U256.2
unnamed: U255.6, U256.1
unnamed: U257.5, U258.2
unnamed: U257.6, U258.1
unnamed: U258.5, U259.2
unnamed: U258.6, U259.1
unnamed: U259.5, U260.2
unnamed: U259.6, U260.1
unnamed: U260.5, U261.2
unnamed: U260.6, U261.1
unnamed: U261.5, U262.2
unnamed: U261.6, U262.1
unnamed: U262.5, U263.2
unnamed: U262.6, U263.1
unnamed: U263.5, U264.2
unnamed: U263.6, U264.1
unnamed: U264.5, U265.2
unnamed: U264.6, U265.1
unnamed: U265.5, U266.2
unnamed: U265.6, U266.1
unnamed: U266.5, U267.2
unnamed: U266.6, U267.1
unnamed: U267.5, U268.2
unnamed: U267.6, U268.1
unnamed: U268.5, U269.2
unnamed: U268.6, U269.1
unnamed: U269.5, U270.2
unnamed: U269.6, U270.1
unnamed: U270.5, U271.2
unnamed: U270.6, U271.1
unnamed: U271.5, U272.2
unnamed: U271.6, U272.1
unnamed: U272.5, U273.2
unnamed: U272.6, U273.1
unnamed: U273.5, U274.2
unnamed: U273.6, U274.1
unnamed: U274.5, U275.2
unnamed: U274.6, U275.1
unnamed: U275.5, U276.2
unnamed: U275.6, U276.1
unnamed: U276.5, U277.2
unnamed: U276.6, U277.1
unnamed: U277.5, U278.2
unnamed: U277.6, U278.1
unnamed: U278.5, U279.2
unnamed: U278.6, U279.1
unnamed: U279.5, U280.2
unnamed: U279.6, U280.1
unnamed: U280.5, U281.2
unnamed: U280.6, U281.1
unnamed: U281.5, U282.2
unnamed: U281.6, U282.1
unnamed: U282.5, U283.2
unnamed: U282.6, U283.1
unnamed: U283.5, U284.2
unnamed: U283.6, U284.1
unnamed: U284.5, U285.2
unnamed: U284.6, U285.1
unnamed: U285.5, U286.2
unnamed: U285.6, U286.1
unnamed: U286.5, U287.2
unnamed: U286.6, U287.1
unnamed: U287.5, U288.2
unnamed: U287.6, U288.1
unnamed: U288.5, U289.2
unnamed: U288.6, U289.1
unnamed: U289.5, U290.2
unnamed: U289.6, U290.1
unnamed: U290.5, U291.2
unnamed: U290.6, U291.1
unnamed: U291.5, U292.2
unnamed: U291.6, U292.1
unnamed: U292.5, U293.2
unnamed: U292.6, U293.1
unnamed: U293.5, U294.2
unnamed: U293.6, U294.1
unnamed: U294.5, U295.2
unnamed: U294.6, U295.1
unnamed: U295.5, U296.2
unnamed: U295.6, U296.1
unnamed: U296.5, U297.2
unnamed: U296.6, U297.1
unnamed: U297.5, U298.2
unnamed: U297.6, U298.1
unnamed: U298.5, U299.2
unnamed: U298.6, U299.1
unnamed: U299.5, U300.2
unnamed: U299.6, U300.1
unnamed: U300.5, U301.2
unnamed: U300.6, U301.1
unnamed: U301.5, U302.2
unnamed: U301.6, U302.1
unnamed: U302.5, U303.2
unnamed: U302.6, U303.1
unnamed: U303.5, U304.2
unnamed: U303.6, U304.1
unnamed: U304.5, U305.2
unnamed: U304.6, U305.1
unnamed: U305.5, U306.2
unnamed: U305.6, U306.1
unnamed: U306.5, U307.2
unnamed: U306.6, U307.1
unnamed: U307.5, U308.2
unnamed: U307.6, U308.1
unnamed: U308.5, U309.2
unnamed: U308.6, U309.1
unnamed: U309.5, U310.2
unnamed: U309.6, U310.1
unnamed: U310.5, U311.2
unnamed: U310.6, U311.1
unnamed: U311.5, U312.2
unnamed: U311.6, U312.1
unnamed: U312.5, U313.2
unnamed: U312.6, U313.1
unnamed: U313.5, U314.2
unnamed: U313.6, U314.1
unnamed: U314.5, U315.2
unnamed: U314.6, U315.1
unnamed: U315.5, U316.2
unnamed: U315.6, U316.1
unnamed: U316.5, U317.2
unnamed: U316.6, U317.1
unnamed: U317.5, U318.2
unnamed: U317.6, U318.1
unnamed: U318.5, U319.2
unnamed: U318.6, U319.1
unnamed: U319.5, U320.2
unnamed: U319.6, U320.1
unnamed: U321.5, U322.2
unnamed: U321.6, U322.1
unnamed: U322.5, U323.2
unnamed: U322.6, U323.1
unnamed: U323.5, U324.2
unnamed: U323.6, U324.1
unnamed: U324.5, U325.2
unnamed: U324.6, U325.1
unnamed: U325.5, U326.2
unnamed: U325.6, U326.1
unnamed: U326.5, U327.2
unnamed: U326.6, U327.1
unnamed: U327.5, U328.2
unnamed: U327.6, U328.1
unnamed: U328.5, U329.2
unnamed: U328.6, U329.1
unnamed: U329.5, U330.2
unnamed: U329.6, U330.1
unnamed: U330.5, U331.2
unnamed: U330.6, U331.1
unnamed: U331.5, U332.2
unnamed: U331.6, U332.1
unnamed: U332.5, U333.2
unnamed: U332.6, U333.1
unnamed: U333.5, U334.2
unnamed: U333.6, U334.1
unnamed: U334.5, U335.2
unnamed: U334.6, U335.1
unnamed: U335.5, U336.2
unnamed: U335.6, U336.1
unnamed: U336.5, U337.2
unnamed: U336.6, U337.1
unnamed: U337.5, U338.2
unnamed: U337.6, U338.1
unnamed: U338.5, U339.2
unnamed: U338.6, U339.1
unnamed: U339.5, U340.2
unnamed: U339.6, U340.1
unnamed: U340.5, U341.2
unnamed: U340.6, U341.1
unnamed: U341.5, U342.2
unnamed: U341.6, U342.1
unnamed: U342.5, U343.2
unnamed: U342.6, U343.1
unnamed: U343.5, U344.2
unnamed: U343.6, U344.1
unnamed: U344.5, U345.2
unnamed: U344.6, U345.1
unnamed: U345.5, U346.2
unnamed: U345.6, U346.1
unnamed: U346.5, U347.2
unnamed: U346.6, U347.1
unnamed: U347.5, U348.2
unnamed: U347.6, U348.1
unnamed: U348.5, U349.2
unnamed: U348.6, U349.1
unnamed: U349.5, U350.2
unnamed: U349.6, U350.1
unnamed: U350.5, U351.2
unnamed: U350.6, U351.1
unnamed: U351.5, U352.2
unnamed: U351.6, U352.1
unnamed: U352.5, U353.2
unnamed: U352.6, U353.1
unnamed: U353.5, U354.2
unnamed: U353.6, U354.1
unnamed: U354.5, U355.2
unnamed: U354.6, U355.1
unnamed: U355.5, U356.2
unnamed: U355.6, U356.1
unnamed: U356.5, U357.2
unnamed: U356.6, U357.1
unnamed: U357.5, U358.2
unnamed: U357.6, U358.1
unnamed: U358.5, U359.2
unnamed: U358.6, U359.1
unnamed: U359.5, U360.2
unnamed: U359.6, U360.1
unnamed: U360.5, U361.2
unnamed: U360.6, U361.1
unnamed: U361.5, U362.2
unnamed: U361.6, U362.1
unnamed: U362.5, U363.2
unnamed: U362.6, U363.1
unnamed: U363.5, U364.2
unnamed: U363.6, U364.1
unnamed: U364.5, U365.2
unnamed: U364.6, U365.1
unnamed: U365.5, U366.2
unnamed: U365.6, U366.1
unnamed: U366.5, U367.2
unnamed: U366.6, U367.1
unnamed: U367.5, U368.2
unnamed: U367.6, U368.1
unnamed: U368.5, U369.2
unnamed: U368.6, U369.1
unnamed: U369.5, U370.2
unnamed: U369.6, U370.1
unnamed: U370.5, U371.2
unnamed: U370.6, U371.1
unnamed: U371.5, U372.2
unnamed: U371.6, U372.1
unnamed: U372.5, U373.2
unnamed: U372.6, U373.1
unnamed: U373.5, U374.2
unnamed: U373.6, U374.1
unnamed: U374.5, U375.2
unnamed: U374.6, U375.1
unnamed: U375.5, U376.2
unnamed: U375.6, U376.1
unnamed: U376.5, U377.2
unnamed: U376.6, U377.1
unnamed: U377.5, U378.2
unnamed: U377.6, U378.1
unnamed: U378.5, U379.2
unnamed: U378.6, U379.1
unnamed: U379.5, U380.2
unnamed: U379.6, U380.1
unnamed: U380.5, U381.2
unnamed: U380.6, U381.1
unnamed: U381.5, U382.2
unnamed: U381.6, U382.1
unnamed: U382.5, U383.2
unnamed: U382.6, U383.1
unnamed: U383.5, U384.2
unnamed: U383.6, U384.1
unnamed: U385.5, U386.2
unnamed: U385.6, U386.1
unnamed: U386.5, U387.2
unnamed: U386.6, U387.1
unnamed: U387.5, U388.2
unnamed: U387.6, U388.1
unnamed: U388.5, U389.2
unnamed: U388.6, U389.1
unnamed: U389.5, U390.2
unnamed: U389.6, U390.1
unnamed: U390.5, U391.2
unnamed: U390.6, U391.1
unnamed: U391.5, U392.2
unnamed: U391.6, U392.1
unnamed: U392.5, U393.2
unnamed: U392.6, U393.1
unnamed: U393.5, U394.2
unnamed: U393.6, U394.1
unnamed: U394.5, U395.2
unnamed: U394.6, U395.1
unnamed: U395.5, U396.2
unnamed: U395.6, U396.1
unnamed: U396.5, U397.2
unnamed: U396.6, U397.1
unnamed: U397.5, U398.2
unnamed: U397.6, U398.1
unnamed: U398.5, U399.2
unnamed: U398.6, U399.1
unnamed: U399.5, U400.2
unnamed: U399.6, U400.1
unnamed: U400.5, U401.2
unnamed: U400.6, U401.1
unnamed: U401.5, U402.2
unnamed: U401.6, U402.1
unnamed: U402.5, U403.2
unnamed: U402.6, U403.1
unnamed: U403.5, U404.2
unnamed: U403.6, U404.1
unnamed: U404.5, U405.2
unnamed: U404.6, U405.1
unnamed: U405.5, U406.2
unnamed: U405.6, U406.1
unnamed: U406.5, U407.2
unnamed: U406.6, U407.1
unnamed: U407.5, U408.2
unnamed: U407.6, U408.1
unnamed: U408.5, U409.2
unnamed: U408.6, U409.1
unnamed: U409.5, U410.2
unnamed: U409.6, U410.1
unnamed: U410.5, U411.2
unnamed: U410.6, U411.1
unnamed: U411.5, U412.2
unnamed: U411.6, U412.1
unnamed: U412.5, U413.2
unnamed: U412.6, U413.1
unnamed: U413.5, U414.2
unnamed: U413.6, U414.1
unnamed: U414.5, U415.2
unnamed: U414.6, U415.1
unnamed: U415.5, U416.2
unnamed: U415.6, U416.1
unnamed: U416.5, U417.2
unnamed: U416.6, U417.1
unnamed: U417.5, U418.2
unnamed: U417.6, U418.1
unnamed: U418.5, U419.2
unnamed: U418.6, U419.1
unnamed: U419.5, U420.2
unnamed: U419.6, U420.1
unnamed: U420.5, U421.2
unnamed: U420.6, U421.1
unnamed: U421.5, U422.2
unnamed: U421.6, U422.1
unnamed: U422.5, U423.2
unnamed: U422.6, U423.1
unnamed: U423.5, U424.2
unnamed: U423.6, U424.1
unnamed: U424.5, U425.2
unnamed: U424.6, U425.1
unnamed: U425.5, U426.2
unnamed: U425.6, U426.1
unnamed: U426.5, U427.2
unnamed: U426.6, U427.1
unnamed: U427.5, U428.2
unnamed: U427.6, U428.1
unnamed: U428.5, U429.2
unnamed: U428.6, U429.1
unnamed: U429.5, U430.2
unnamed: U429.6, U430.1
unnamed: U430.5, U431.2
unnamed: U430.6, U431.1
unnamed: U431.5, U432.2
unnamed: U431.6, U432.1
unnamed: U432.5, U433.2
unnamed: U432.6, U433.1
unnamed: U433.5, U434.2
unnamed: U433.6, U434.1
unnamed: U434.5, U435.2
unnamed: U434.6, U435.1
unnamed: U435.5, U436.2
unnamed: U435.6, U436.1
unnamed: U436.5, U437.2
unnamed: U436.6, U437.1
unnamed: U437.5, U438.2
unnamed: U437.6, U438.1
unnamed: U438.5, U439.2
unnamed: U438.6, U439.1
unnamed: U439.5, U440.2
unnamed: U439.6, U440.1
unnamed: U440.5, U441.2
unnamed: U440.6, U441.1
unnamed: U441.5, U442.2
unnamed: U441.6, U442.1
unnamed: U442.5, U443.2
unnamed: U442.6, U443.1
unnamed: U443.5, U444.2
unnamed: U443.6, U444.1
unnamed: U444.5, U445.2
unnamed: U444.6, U445.1
unnamed: U445.5, U446.2
unnamed: U445.6, U446.1
unnamed: U446.5, U447.2
unnamed: U446.6, U447.1
unnamed: U447.5, U448.2
unnamed: U447.6, U448.1
unnamed: U449.5, U450.2
unnamed: U449.6, U450.1
unnamed: U450.5, U451.2
unnamed: U450.6, U451.1
unnamed: U451.5, U452.2
unnamed: U451.6, U452.1
unnamed: U452.5, U453.2
unnamed: U452.6, U453.1
unnamed: U453.5, U454.2
unnamed: U453.6, U454.1
unnamed: U454.5, U455.2
unnamed: U454.6, U455.1
unnamed: U455.5, U456.2
unnamed: U455.6, U456.1
unnamed: U456.5, U457.2
unnamed: U456.6, U457.1
unnamed: U457.5, U458.2
unnamed: U457.6, U458.1
unnamed: U458.5, U459.2
unnamed: U458.6, U459.1
unnamed: U459.5, U460.2
unnamed: U459.6, U460.1
unnamed: U460.5, U461.2
unnamed: U460.6, U461.1
unnamed: U461.5, U462.2
unnamed: U461.6, U462.1
unnamed: U462.5, U463.2
unnamed: U462.6, U463.1
unnamed: U463.5, U464.2
unnamed: U463.6, U464.1
unnamed: U464.5, U465.2
unnamed: U464.6, U465.1
unnamed: U465.5, U466.2
unnamed: U465.6, U466.1
unnamed: U466.5, U467.2
unnamed: U466.6, U467.1
unnamed: U467.5, U468.2
unnamed: U467.6, U468.1
unnamed: U468.5, U469.2
unnamed: U468.6, U469.1
unnamed: U469.5, U470.2
unnamed: U469.6, U470.1
unnamed: U470.5, U471.2
unnamed: U470.6, U471.1
unnamed: U471.5, U472.2
unnamed: U471.6, U472.1
unnamed: U472.5, U473.2
unnamed: U472.6, U473.1
unnamed: U473.5, U474.2
unnamed: U473.6, U474.1
unnamed: U474.5, U475.2
unnamed: U474.6, U475.1
unnamed: U475.5, U476.2
unnamed: U475.6, U476.1
unnamed: U476.5, U477.2
unnamed: U476.6, U477.1
unnamed: U477.5, U478.2
unnamed: U477.6, U478.1
unnamed: U478.5, U479.2
unnamed: U478.6, U479.1
unnamed: U479.5, U480.2
unnamed: U479.6, U480.1
unnamed: U480.5, U481.2
unnamed: U480.6, U481.1
unnamed: U481.5, U482.2
unnamed: U481.6, U482.1
unnamed: U482.5, U483.2
unnamed: U482.6, U483.1
unnamed: U483.5, U484.2
unnamed: U483.6, U484.1
unnamed: U484.5, U485.2
unnamed: U484.6, U485.1
unnamed: U485.5, U486.2
unnamed: U485.6, U486.1
unnamed: U486.5, U487.2
unnamed: U486.6, U487.1
unnamed: U487.5, U488.2
unnamed: U487.6, U488.1
unnamed: U488.5, U489.2
unnamed: U488.6, U489.1
unnamed: U489.5, U490.2
unnamed: U489.6, U490.1
unnamed: U490.5, U491.2
unnamed: U490.6, U491.1
unnamed: U491.5, U492.2
unnamed: U491.6, U492.1
unnamed: U492.5, U493.2
unnamed: U492.6, U493.1
unnamed: U493.5, U494.2
unnamed: U493.6, U494.1
unnamed: U494.5, U495.2
unnamed: U494.6, U495.1
unnamed: U495.5, U496.2
unnamed: U495.6, U496.1
unnamed: U496.5, U497.2
unnamed: U496.6, U497.1
unnamed: U497.5, U498.2
unnamed: U497.6, U498.1
unnamed: U498.5, U499.2
unnamed: U498.6, U499.1
unnamed: U499.5, U500.2
unnamed: U499.6, U500.1
unnamed: U500.5, U501.2
unnamed: U500.6, U501.1
unnamed: U501.5, U502.2
unnamed: U501.6, U502.1
unnamed: U502.5, U503.2
unnamed: U502.6, U503.1
unnamed: U503.5, U504.2
unnamed: U503.6, U504.1
unnamed: U504.5, U505.2
unnamed: U504.6, U505.1
unnamed: U505.5, U506.2
unnamed: U505.6, U506.1
unnamed: U506.5, U507.2
unnamed: U506.6, U507.1
unnamed: U507.5, U508.2
unnamed: U507.6, U508.1
unnamed: U508.5, U509.2
unnamed: U508.6, U509.1
unnamed: U509.5, U510.2
unnamed: U509.6, U510.1
unnamed: U510.5, U511.2
unnamed: U510.6, U511.1
unnamed: U511.5, U512.2
unnamed: U511.6, U512.1

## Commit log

2016-02-24 APA102C 8x64 Panel
